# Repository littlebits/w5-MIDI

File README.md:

Copyright 2014 littleBits Electronics.

littleBits, littleBits logo, Bits, cloudBit, are trademarks of littleBits Electronic Inc. 

littleBits Electronics, Inc. supports the Open Source Hardware Statement of Principles by making the circuit designs for its modules available pursuant to the CERN Hardware License, Version 1.2.

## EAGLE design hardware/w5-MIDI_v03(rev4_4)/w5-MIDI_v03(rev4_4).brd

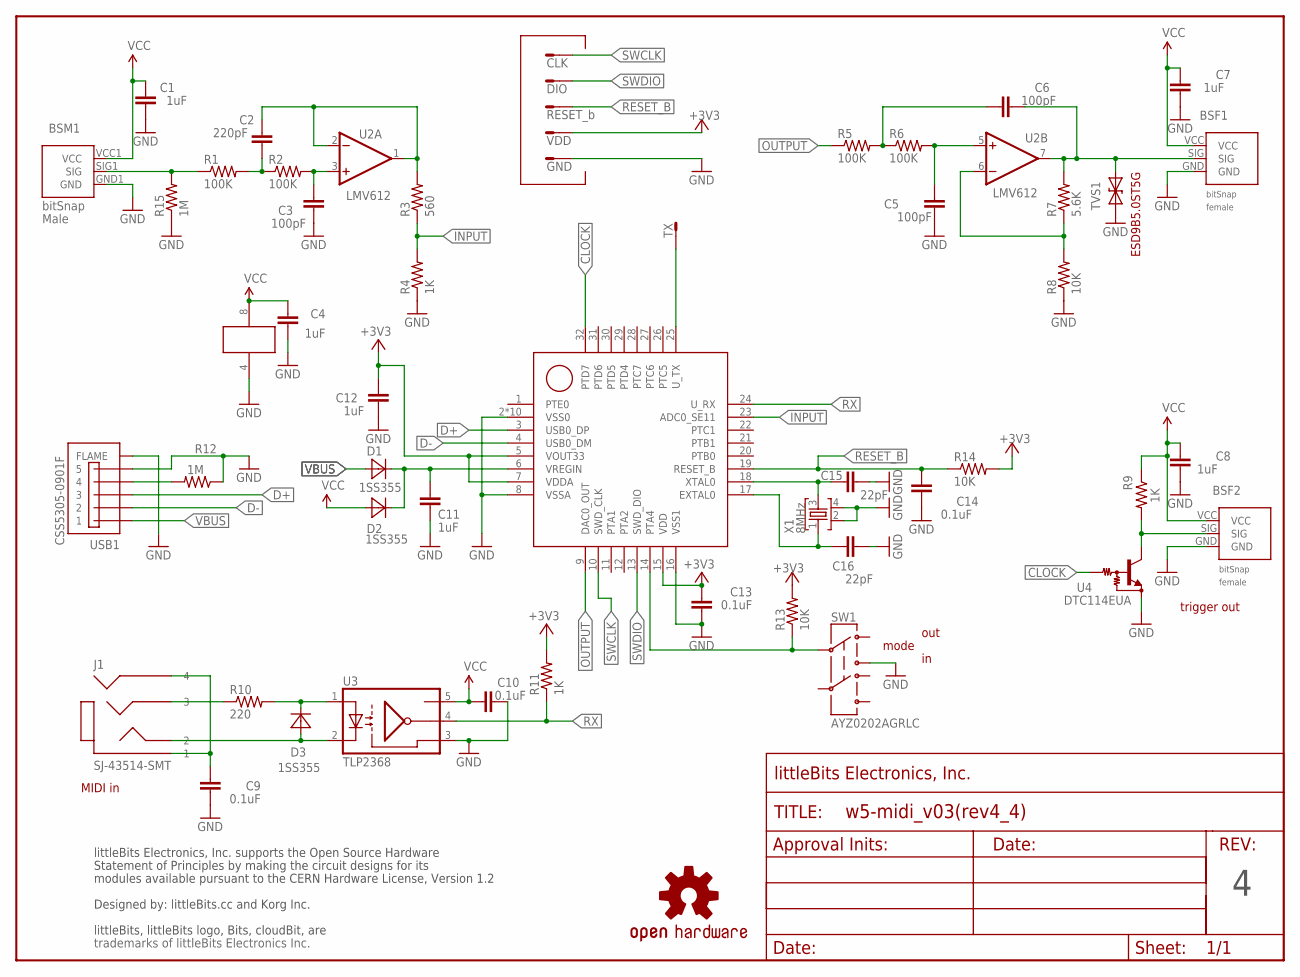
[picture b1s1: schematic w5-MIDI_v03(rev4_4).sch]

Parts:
BSF1, BSF2: BITSNAP_V03_FEMALE
BSM1: BITSNAP_V03_MALE
C1, C4, C7, C8, C11, C12: 1uF; CC_1608_0.8_TBR_LB_1PRIMARY
C2: 220pF; CC_1608_0.8_TBR_LB_1PRIMARY
C3, C5, C6: 100pF; CC_1608_0.8_TBR_LB_1PRIMARY
C9, C10, C13, C14: 0.1uF; CC_1608_0.8_TBR_LB_1PRIMARY
C15, C16: 22pF; CC_1608_0.8_TBR_LB_1PRIMARY
D1, D2, D3: 1SS355; DISC_ROHM-UMD2_#_TBR_LB_1PRIMARY
FRAME1: FRAME-LETTER-OHWOHW; FABDWG01-OHW
J1: SJ-43514-SMT; LB_K_CN_SJ-43514-SMT_LB
R1, R2, R5, R6: 100K; R_1608_LB
R3: 560; R_1608_LB
R4, R9, R11: 1K; R_1608_LB
R7: 5.6K; R_1608_LB
R8, R13, R14: 10K; R_1608_LB
R10: 220; R_1608_LB
R12: 1M; R_1608_LB
R15: 1M; RES-0402
SW1: AYZ0202AGRLC; SW_MS-22C01_#_TBR_LB_1PRIMARY
TVS1: DIODE-TVSSOD-923; SOD-923
U1: MKL26Z64VFM4; IC_TI-QFN32_0.5_TBR_LB_1PRIMARY
U2: LMV612; IC_TSSOP8-DCK_0.65_TBR_LB_1PRIMARY
U3: TLP2368; PC_PS9117-F3-A_#_TBR_LB_1PRIMARY
U4: DTC114EUA; DISC_SC-70_#_TBR_LB_1PRIMARY
U$1: OSHWCREDIT-KORG
U$5: OSHW-LOGOL; OSHW-LOGO-L
USB1: CSS5305-0901F; MICRO-USB-FRONT-DIP-REAR-SMD
W5JP1: GND; TEST_POINT_1PRIMARY
W5JP2: VDD; TEST_POINT_1PRIMARY
W5JP3: RESET_b; TEST_POINT_1PRIMARY
W5JP4: DIO; TEST_POINT_1PRIMARY
W5JP5: CLK; TEST_POINT_1PRIMARY
W5JP6: TX; TEST_POINT_1PRIMARY
X1: 8MHz; X_ROSON_RT5_#_TBR_LB_1PRIMARY

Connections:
+3V3: C12.2, C13.2, R11.2, R13.2, R14.2, U1.5 (VOUT33), U1.7 (VDDA), U1.15 (VDD), W5JP2.1
CLOCK: U1.32 (PTD7), U4.1 (B)
D+: U1.3 (USB0_DP), USB1.3
D-: U1.4 (USB0_DM), USB1.2
GND: BSF1.GND, BSF2.GND, BSM1.GND1 (GND), C1.2, C3.1, C4.1, C5.1, C7.1, C8.1, C9.1, C10.2, C11.2, C12.1, C13.1, C14.1, C15.1, C16.1, R4.1, R8.1, R12.1, R15.1, SW1.3, TVS1.1 (A), U1.2 (VSS0), U1.8 (VSSA), U1.16 (VSS1), U1.33 (VSS0), U1.34 (VSS0), U1.35 (VSS0), U1.36 (VSS0), U1.37 (VSS0), U1.38 (VSS0), U1.39 (VSS0), U1.40 (VSS0), U1.41 (VSS0), U2.4 (V-), U3.3 (GND), U4.2 (E), USB1.5, USB1.6 (FLAME), USB1.7 (FLAME), USB1.8 (FLAME), USB1.9 (FLAME), USB1.10 (FLAME), USB1.11 (FLAME), W5JP1.1, X1.2, X1.4
INPUT: R3.1, R4.2, U1.23 (ADC0_SE11)
unnamed: BSM1.SIG1 (SIG), R1.1, R15.2
unnamed: C2.2, R3.2, U2.1 (OUT), U2.2 (-IN)
unnamed: C3.2, R2.2, U2.3 (+IN)
unnamed: C2.1, R1.2, R2.1
unnamed: C9.2, J1.1, J1.4
unnamed: BSF1.SIG, C6.1, R7.2, TVS1.2 (C), U2.7 (OUT)
unnamed: D3.1, J1.2, U3.2 (C)
unnamed: C11.1, D1.2, D2.2, U1.6 (VREGIN)
unnamed: C6.2, R5.2, R6.1
unnamed: C5.2, R6.2, U2.5 (+IN)
unnamed: R13.1, SW1.2, U1.14 (PTA4)
unnamed: D3.2, R10.2, U3.1 (A)
unnamed: R12.2, USB1.4
unnamed: C16.2, U1.17 (EXTAL0), X1.1
unnamed: C15.2, U1.18 (XTAL0), X1.3
unnamed: J1.3, R10.1
unnamed: BSF2.SIG, R9.2, U4.3 (C)
unnamed: R7.1, R8.2, U2.6 (-IN)
OUTPUT: R5.1, U1.9 (DAC0_OUT)
RESET_B: C14.2, R14.1, U1.19 (RESET_B), W5JP3.1
RX: R11.1, U1.24 (U_RX), U3.4 (VO)
SWCLK: U1.10 (SWD_CLK), W5JP5.1
SWDIO: U1.13 (SWD_DIO), W5JP4.1
TX: U1.25 (U_TX), W5JP6.1
VBUS: D1.1, USB1.1
VCC: BSF1.VCC, BSF2.VCC, BSM1.VCC1 (VCC), C1.1, C4.2, C7.2, C8.2, C10.1, D2.1, R9.1, U2.8 (V+), U3.5 (VCC)

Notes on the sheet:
out
mode
trigger out
MIDI in

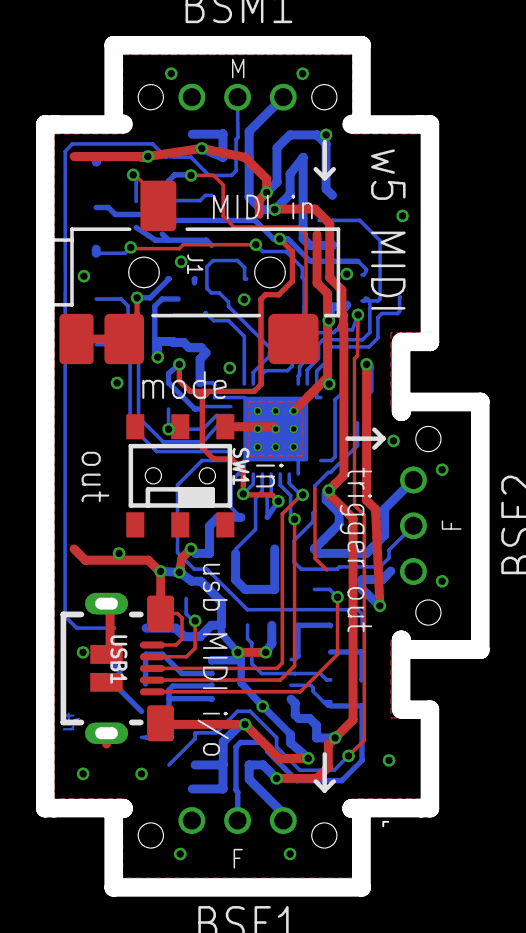
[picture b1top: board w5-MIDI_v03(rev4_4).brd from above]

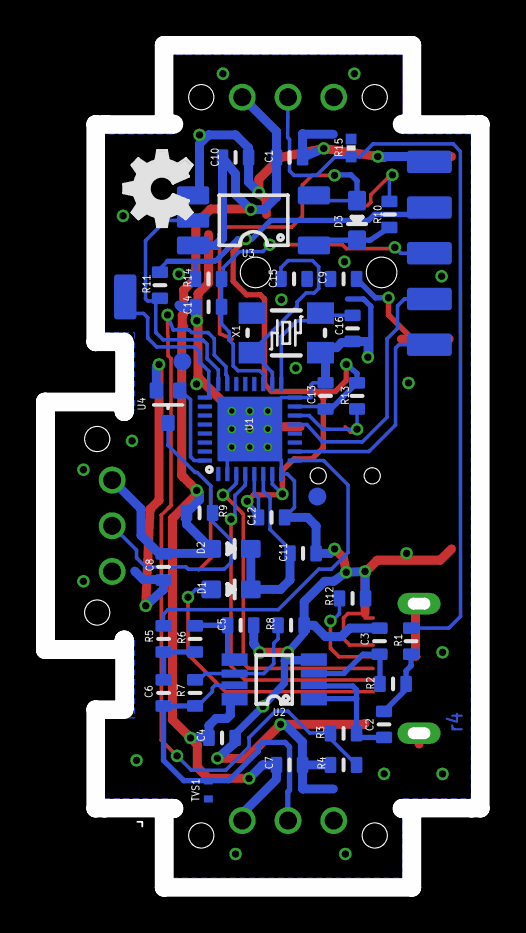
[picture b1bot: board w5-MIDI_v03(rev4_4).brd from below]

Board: 2 copper layers, 24.2 x 46.8 mm, 56 parts (46 on the bottom side), 32 nets.

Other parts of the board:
E$45: OSHW_FILLX150_NOTEXT

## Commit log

2015-04-21 First commit, added hardware files
